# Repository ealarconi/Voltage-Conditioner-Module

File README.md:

# Voltage-Conditioner-Module
Modulo acondicionador de voltaje para DAQ's

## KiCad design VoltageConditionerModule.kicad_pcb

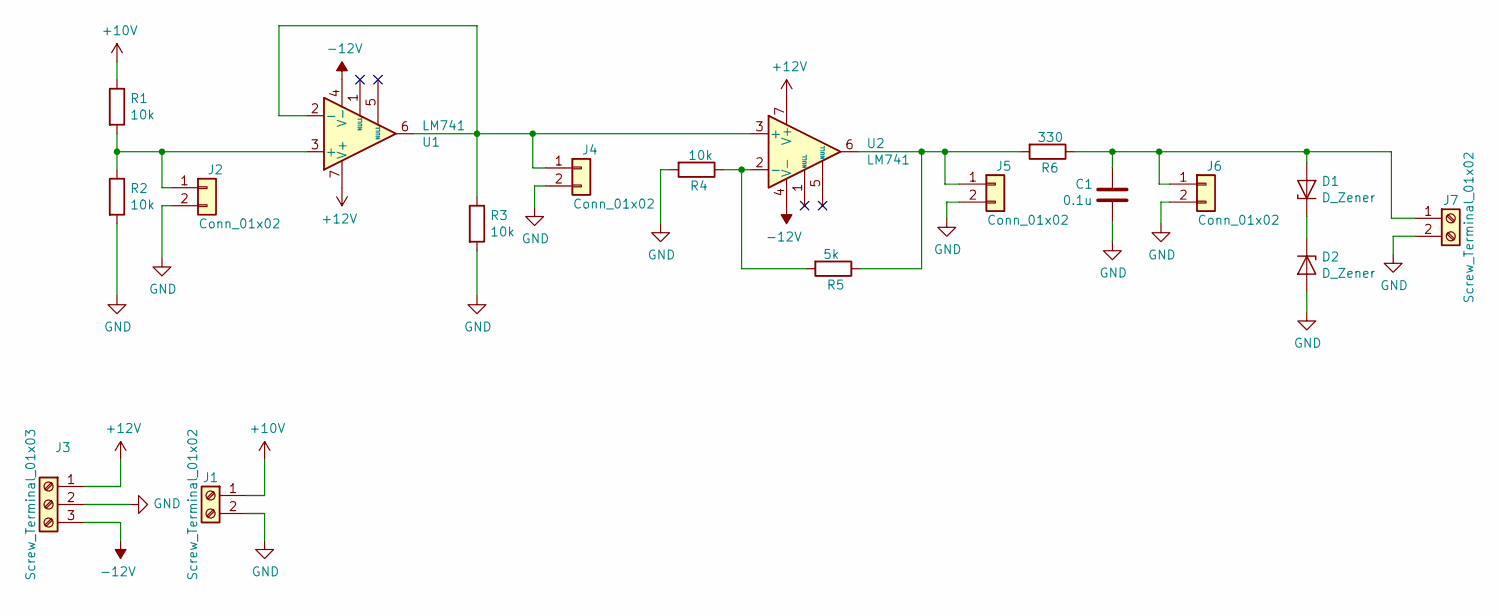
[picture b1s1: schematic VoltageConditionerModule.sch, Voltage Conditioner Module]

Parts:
C1: 0.1u; C_Disc_D4.7mm_W2.5mm_P5.00mm
D1, D2: D_Zener; D_DO-34_SOD68_P7.62mm_Horizontal
J1, J7: Screw_Terminal_01x02; TerminalBlock_bornier-2_P5.08mm
J2, J4, J5, J6: Conn_01x02; PinSocket_1x02_P1.00mm_Vertical
J3: Screw_Terminal_01x03; TerminalBlock_bornier-3_P5.08mm
R1, R2, R3, R4: 10k; R_Axial_DIN0207_L6.3mm_D2.5mm_P10.16mm_Horizontal
R5: 5k; R_Axial_DIN0207_L6.3mm_D2.5mm_P10.16mm_Horizontal
R6: 330; R_Axial_DIN0207_L6.3mm_D2.5mm_P10.16mm_Horizontal
U1, U2: LM741; DIP-8_W7.62mm_LongPads

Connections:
+10V: J1.1, R1.1
+12V: J3.1, U1.7 (V+), U2.7 (V+)
-12V: J3.3, U1.4 (V-), U2.4 (V-)
GND: C1.2, D2.2 (A), J1.2, J2.2, J3.2, J4.2, J5.2, J6.2, J7.2, R2.2, R3.2, R4.2
unnamed: C1.1, D1.2 (A), J6.1, J7.1, R6.1
unnamed: D1.1 (K), D2.1 (K)
unnamed: J2.1, R1.2, R2.1, U1.3 (+)
unnamed: J4.1, R3.1, U1.2 (-), U1.6, U2.3 (+)
unnamed: J5.1, R5.1, R6.2, U2.6
unnamed: R4.1, R5.2, U2.2 (-)

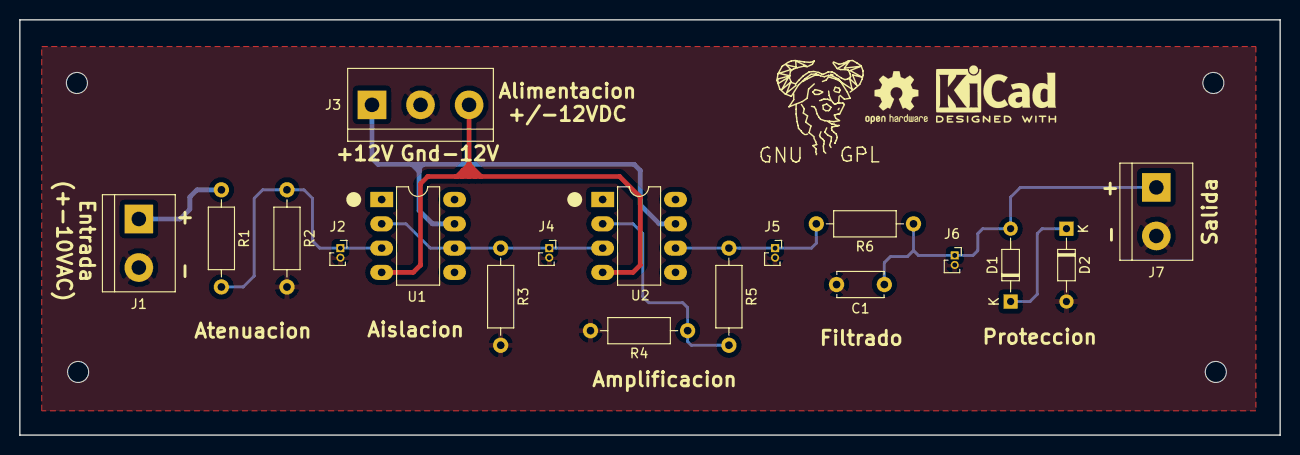
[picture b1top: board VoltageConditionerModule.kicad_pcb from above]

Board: 2 copper layers, 131.8 x 43.4 mm, 18 parts (0 on the bottom side), 10 nets.

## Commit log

2019-02-18 voltage conditioner module -archive-
